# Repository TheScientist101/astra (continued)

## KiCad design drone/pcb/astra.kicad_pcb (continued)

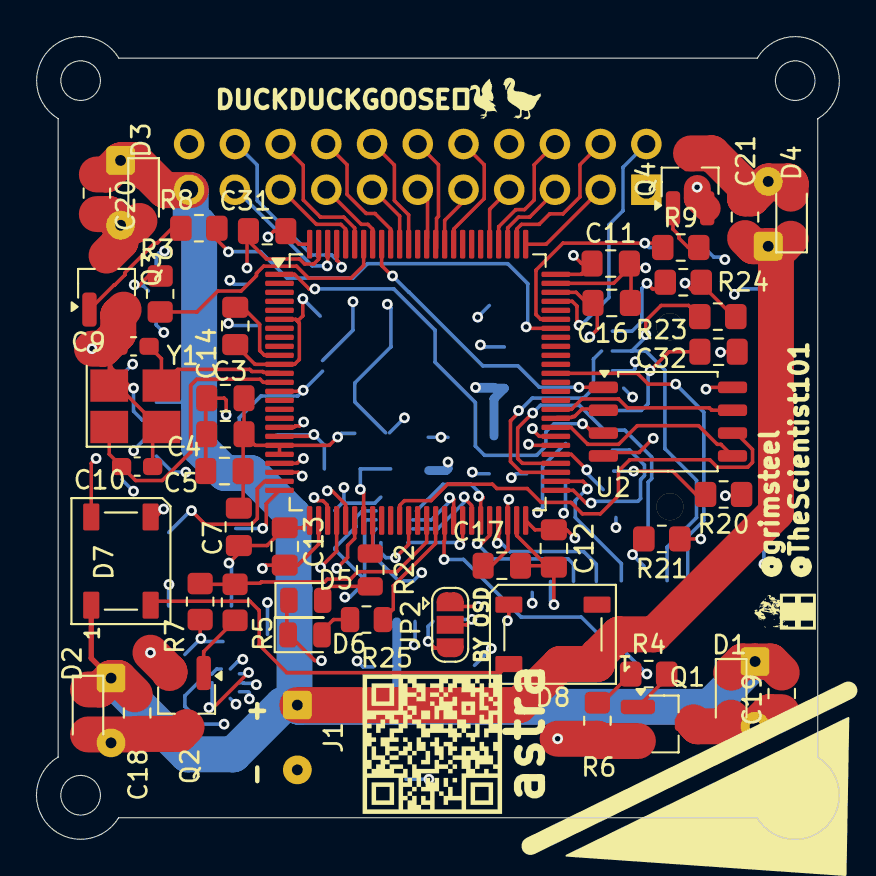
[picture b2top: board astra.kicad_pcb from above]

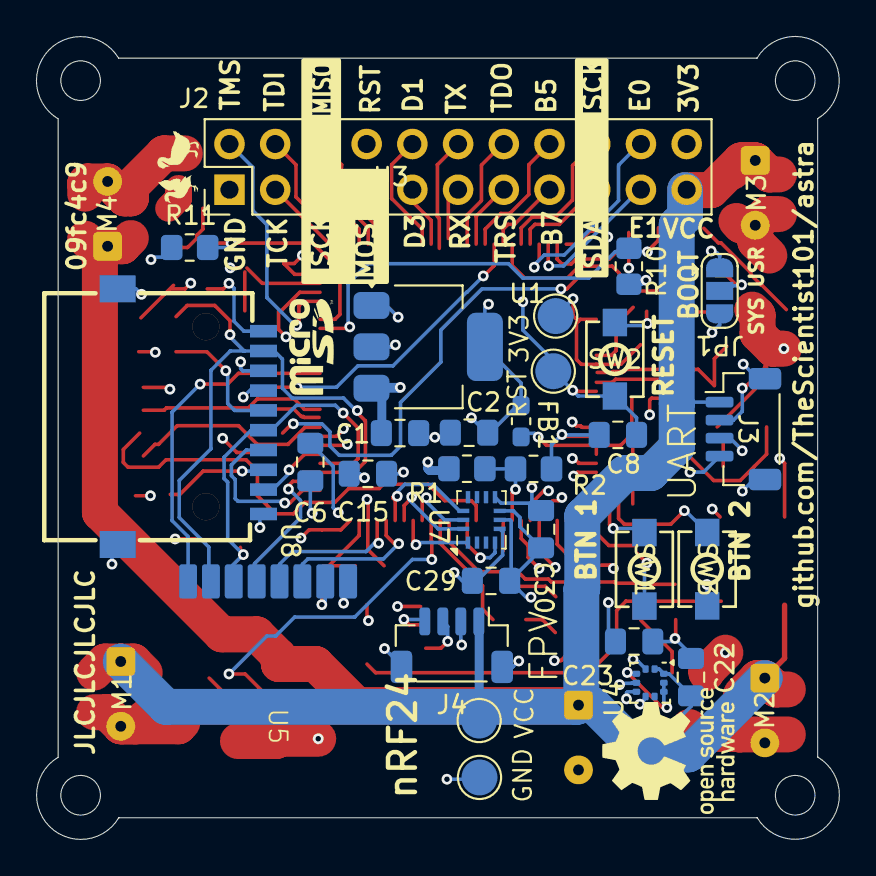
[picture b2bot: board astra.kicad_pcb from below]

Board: 4 copper layers, 44.6 x 44.6 mm, 83 parts (34 on the bottom side), 79 nets.

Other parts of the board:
QR*****: https://github.com/TheScientist101/astra; qrcode

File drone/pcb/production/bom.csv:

Designator,Footprint,Quantity,Value,LCSC Part #
"C1, C2",0805,2,10uF,
"C10, C9",0603,2,3.9pF,
"C11, C12, C13, C14, C18, C19, C20, C21, C22, C23, C29, C30, C31, C32, C4, C6, C7, C8",0805,18,100nF,
C15,0805,1,4.7uF,
"C16, C17",0805,2,0.2uF,
"C3, C5",0805,2,1uF,
"D1, D2, D3, D4",D_SOD-323_HandSoldering,4,1N4148,
"D5, D6",0805,2,LED,
"D7, D8",LED_WS2812B_PLCC4_5.0x5.0mm_P3.2mm,2,WS2812B,
FB1,0603,1,601T05,
J1,SolderWire-0.1sqmm_1x02_P3.6mm_D0.4mm_OD1mm,1,Conn_01x02_Pin,
J2,PinHeader_2x11_P2.54mm_Vertical,1,Conn_02x11_Odd_Even,
"J3, J4",JST_SH_BM04B-SRSS-TB_1x04-1MP_P1.00mm_Vertical,2,Conn_01x04_MountingPin,
"M1, M2, M3, M4",SolderWire-0.1sqmm_1x02_P3.6mm_D0.4mm_OD1mm,4,Motor_DC,
"Q1, Q2, Q3, Q4",SOT-23_Handsoldering,4,AO3400A,
"R1, R2",0805,2,100k,
"R10, R11, R20, R21, R23, R24, R3, R6, R7",0805,9,10k,
"R22, R25",0805,2,1k,
"R4, R5, R8, R9",0805,4,220,
"SW1, SW2, SW3",SW-SMD_L4.0-W2.9-LS5.0,3,SW_Push,
TP4,TestPoint_Pad_D2.0mm,1,TP_GND,
U1,SOT-223-3_TabPin2,1,TLV1117LV33DCYR,
U2,SOIC-8_5.3x5.3mm_P1.27mm,1,W25Q64JVSSIQ_C179171,
U3,LQFP-100_14x14mm_P0.5mm,1,STM32H750VBTx,
U4,ST_HLGA-10_2x2mm_P0.5mm_LayoutBorder3x2y,1,BMP388,
U5,nRF24L01_SMD_Breakout,1,NRF24L01_Breakout,
U7,Bosch_LGA-14_3x2.5mm_P0.5mm,1,BMI270,
U8,SIM-SMD_HYCW110-TF10-180B,1,HYCW110-TF10-180B,
Y1,Crystal_SMD_3225-4Pin_3.2x2.5mm_HandSoldering,1,25 MHz,

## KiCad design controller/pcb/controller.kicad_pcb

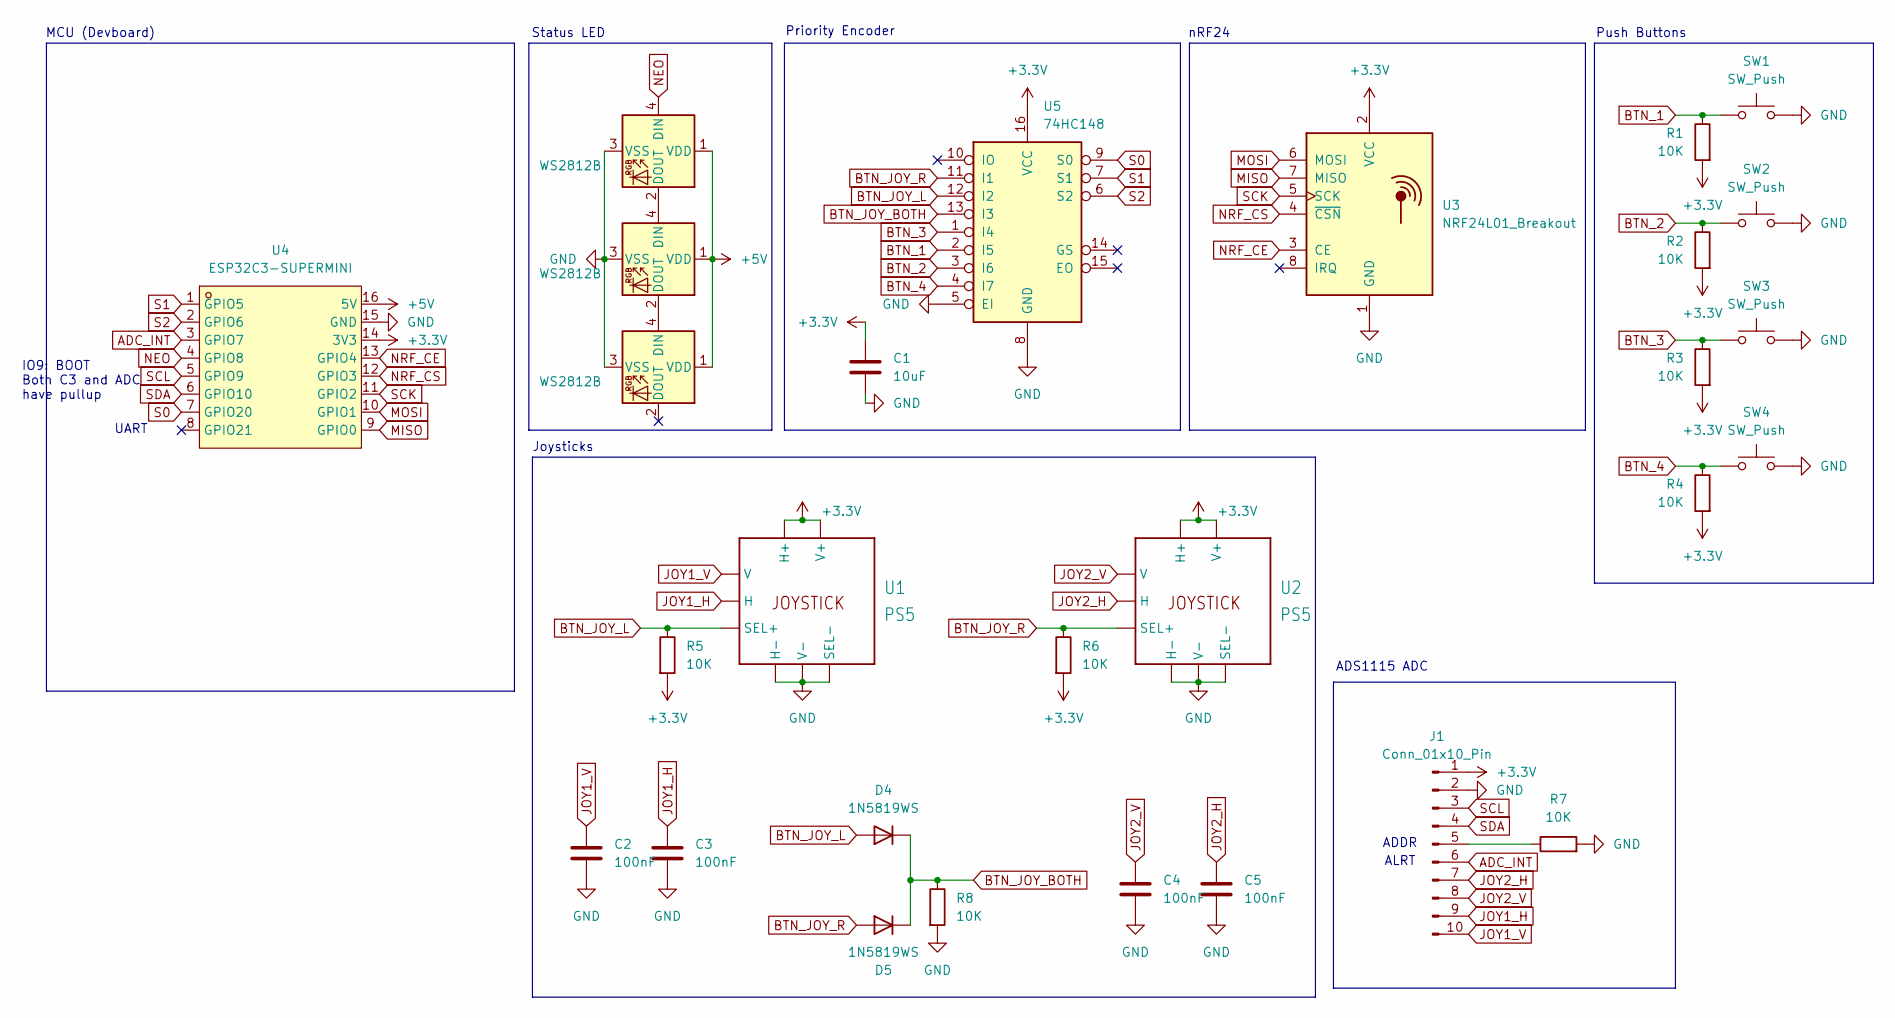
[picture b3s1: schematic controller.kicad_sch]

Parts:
C1: 10uF; C_0805_2012Metric
C2, C3, C4, C5: 100nF; C_0805_2012Metric
D1, D2, D3: WS2812B; LED_WS2812B_PLCC4_5.0x5.0mm_P3.2mm
D4, D5: 1N5819WS; D_DO-41_SOD81_P7.62mm_Horizontal
J1: Conn_01x10_Pin; PinHeader_1x10_P2.54mm_Vertical
R1, R2, R3, R4, R5, R6, R7, R8: 10K; R_0805_2012Metric
SW1, SW2, SW3, SW4: SW_Push; SW_PUSH-12mm
U1, U2: PS5; Joystick
U3: NRF24L01_Breakout; nRF24L01_SMD_Breakout
U4: ESP32C3-SUPERMINI; ESP32-C3-SuperMini; LCSC Part C9900147397
U5: 74HC148; SOP-16_3.9x9.9mm_P1.27mm

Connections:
+3.3V: C1.1, J1.1, R1.2, R2.2, R3.2, R4.2, R5.2, R6.2, U1.3 (H+), U1.3' (V+), U2.3 (H+), U2.3' (V+), U3.2 (VCC), U4.14 (3V3), U5.16 (VCC)
+5V: D1.1 (VDD), D2.1 (VDD), D3.1 (VDD), U4.16 (5V)
ADC_INT: J1.6, U4.3 (GPIO7)
BTN_1: R1.1, SW1.1, U5.2 (I5)
BTN_2: R2.1, SW2.1, U5.3 (I6)
BTN_3: R3.1, SW3.1, U5.1 (I4)
BTN_4: R4.1, SW4.1, U5.4 (I7)
BTN_JOY_BOTH: D4.1 (K), D5.1 (K), R8.1, U5.13 (I3)
BTN_JOY_L: D4.2 (A), R5.1, U1.a (SEL+), U5.12 (I2)
BTN_JOY_R: D5.2 (A), R6.1, U2.a (SEL+), U5.11 (I1)
GND: C1.2, C2.2, C3.2, C4.2, C5.2, D1.3 (VSS), D2.3 (VSS), D3.3 (VSS), J1.2, R7.2, R8.2, SW1.2, SW2.2, SW3.2, SW4.2, U1.1 (H-), U1.1' (V-), U1.c (SEL-), U2.1 (H-), U2.1' (V-), U2.c (SEL-), U3.1 (GND), U4.15 (GND), U5.5 (EI), U5.8 (GND)
JOY1_H: C3.1, J1.9, U1.2 (H)
JOY1_V: C2.1, J1.10, U1.2' (V)
JOY2_H: C5.1, J1.7, U2.2 (H)
JOY2_V: C4.1, J1.8, U2.2' (V)
MISO: U3.7 (MISO), U4.9 (GPIO0)
MOSI: U3.6 (MOSI), U4.10 (GPIO1)
NEO: D1.4 (DIN), U4.4 (GPIO8)
NRF_CE: U3.3 (CE), U4.13 (GPIO4)
NRF_CS: U3.4 (~CSN), U4.12 (GPIO3)
unnamed: D1.2 (DOUT), D2.4 (DIN)
unnamed: D2.2 (DOUT), D3.4 (DIN)
unnamed: J1.5, R7.1
S0: U4.7 (GPIO20), U5.9 (S0)
S1: U4.1 (GPIO5), U5.7 (S1)
S2: U4.2 (GPIO6), U5.6 (S2)
SCK: U3.5 (SCK), U4.11 (GPIO2)
SCL: J1.3, U4.5 (GPIO9)
SDA: J1.4, U4.6 (GPIO10)

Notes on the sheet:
Joysticks
Status LED
Push Buttons
UART
ALRT
nRF24
Priority Encoder
IO9: BOOT Both C3 and ADC have pullup
ADDR
MCU (Devboard)
ADS1115 ADC

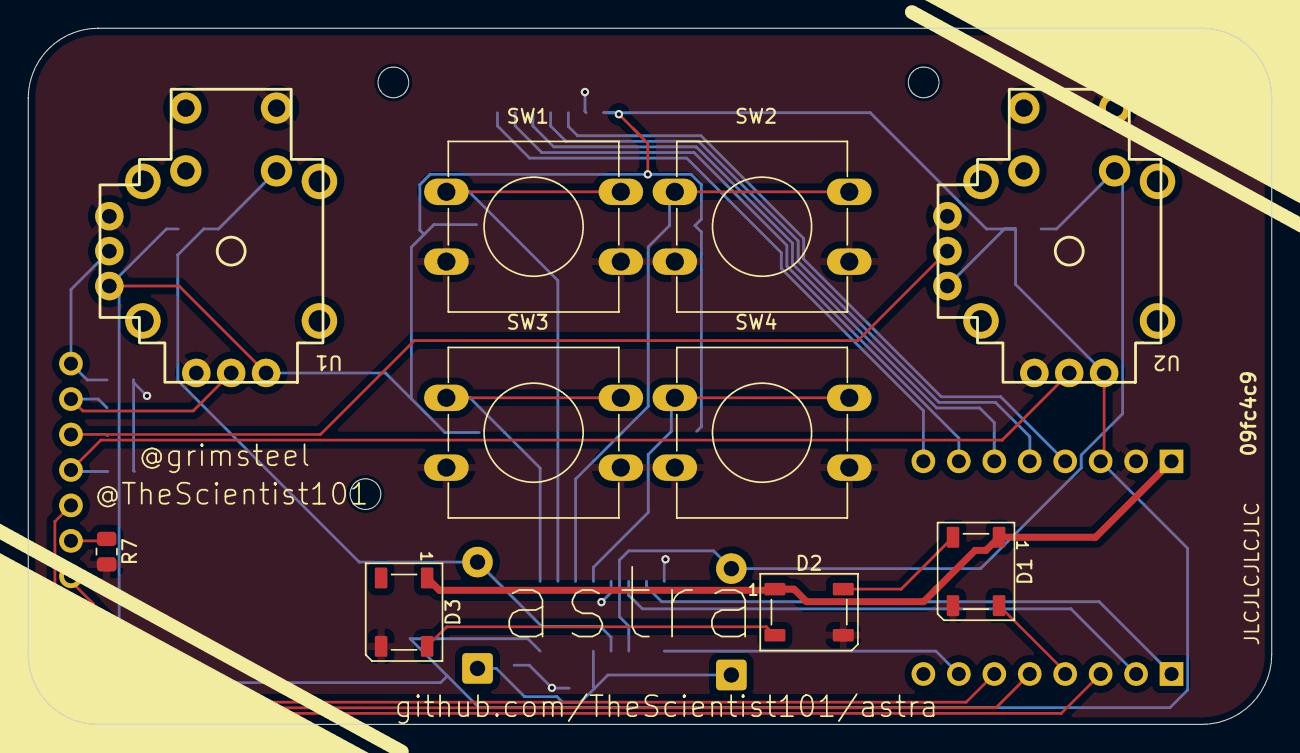
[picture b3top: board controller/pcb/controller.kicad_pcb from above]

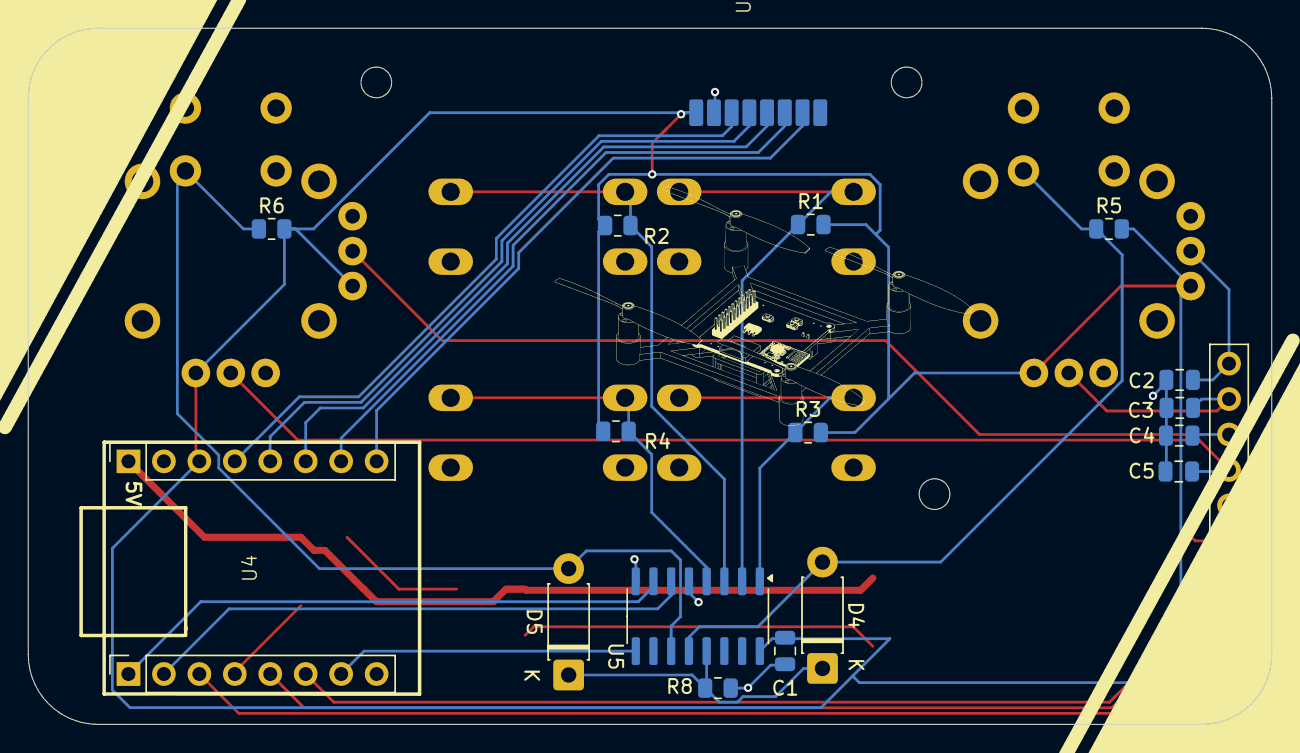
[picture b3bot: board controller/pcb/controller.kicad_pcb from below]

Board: 2 copper layers, 89.1 x 49.9 mm, 28 parts (18 on the bottom side), 29 nets.

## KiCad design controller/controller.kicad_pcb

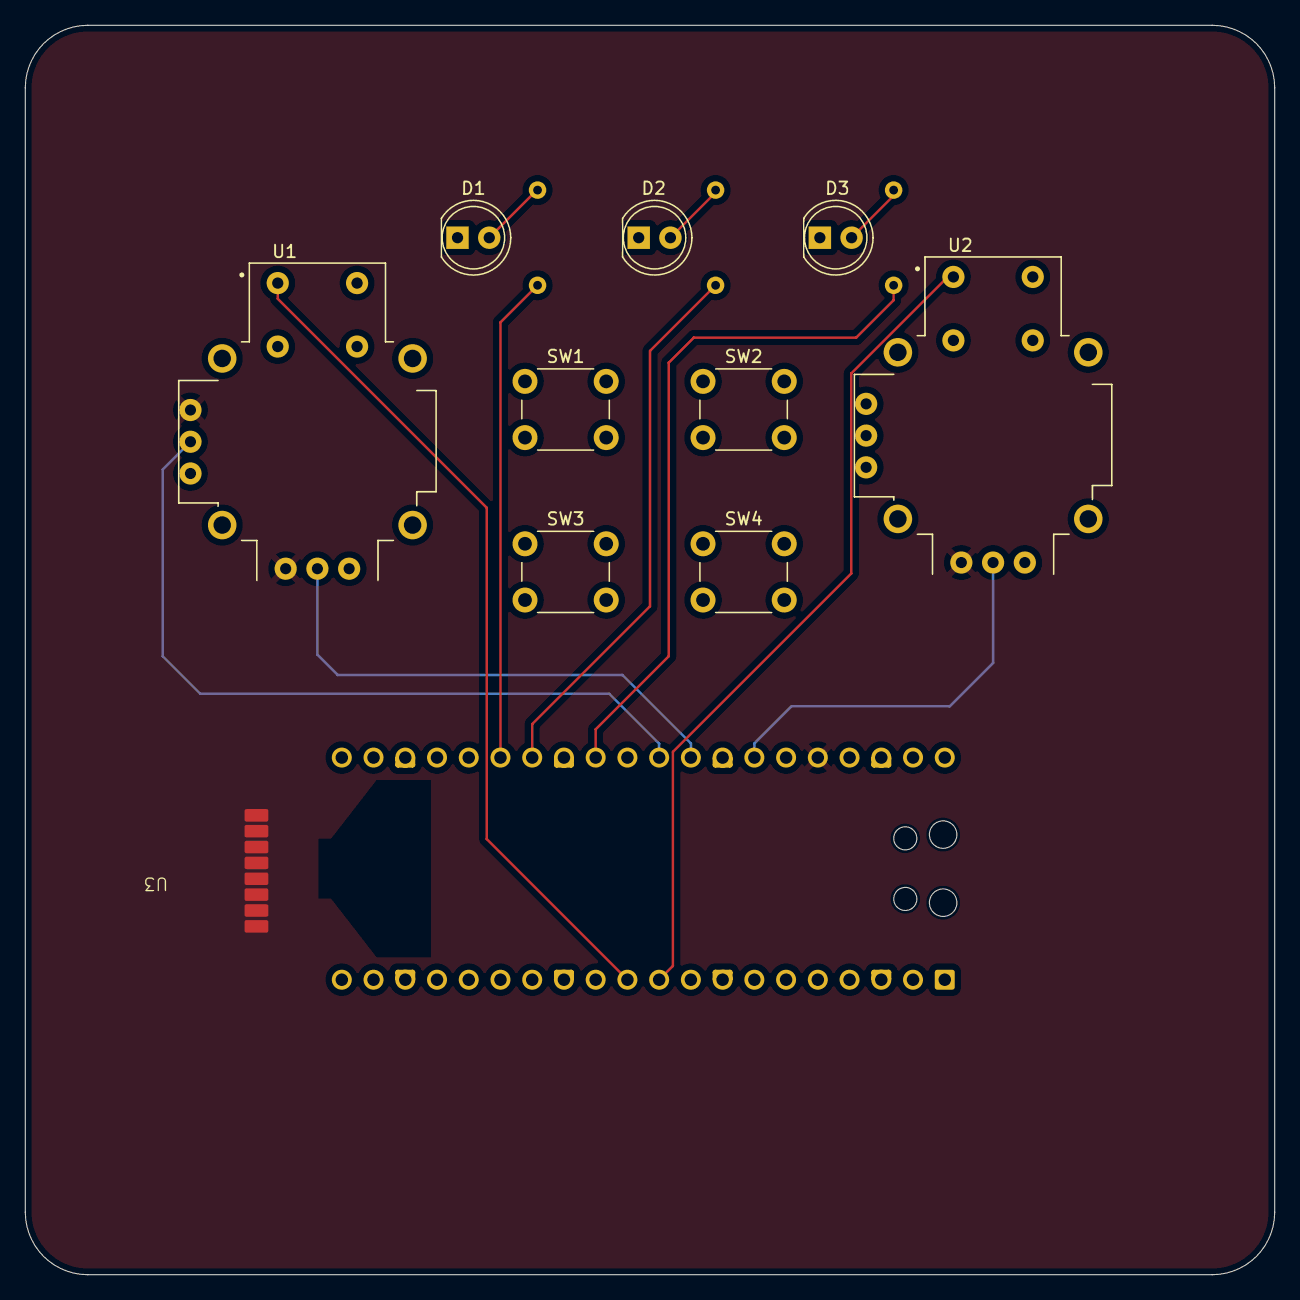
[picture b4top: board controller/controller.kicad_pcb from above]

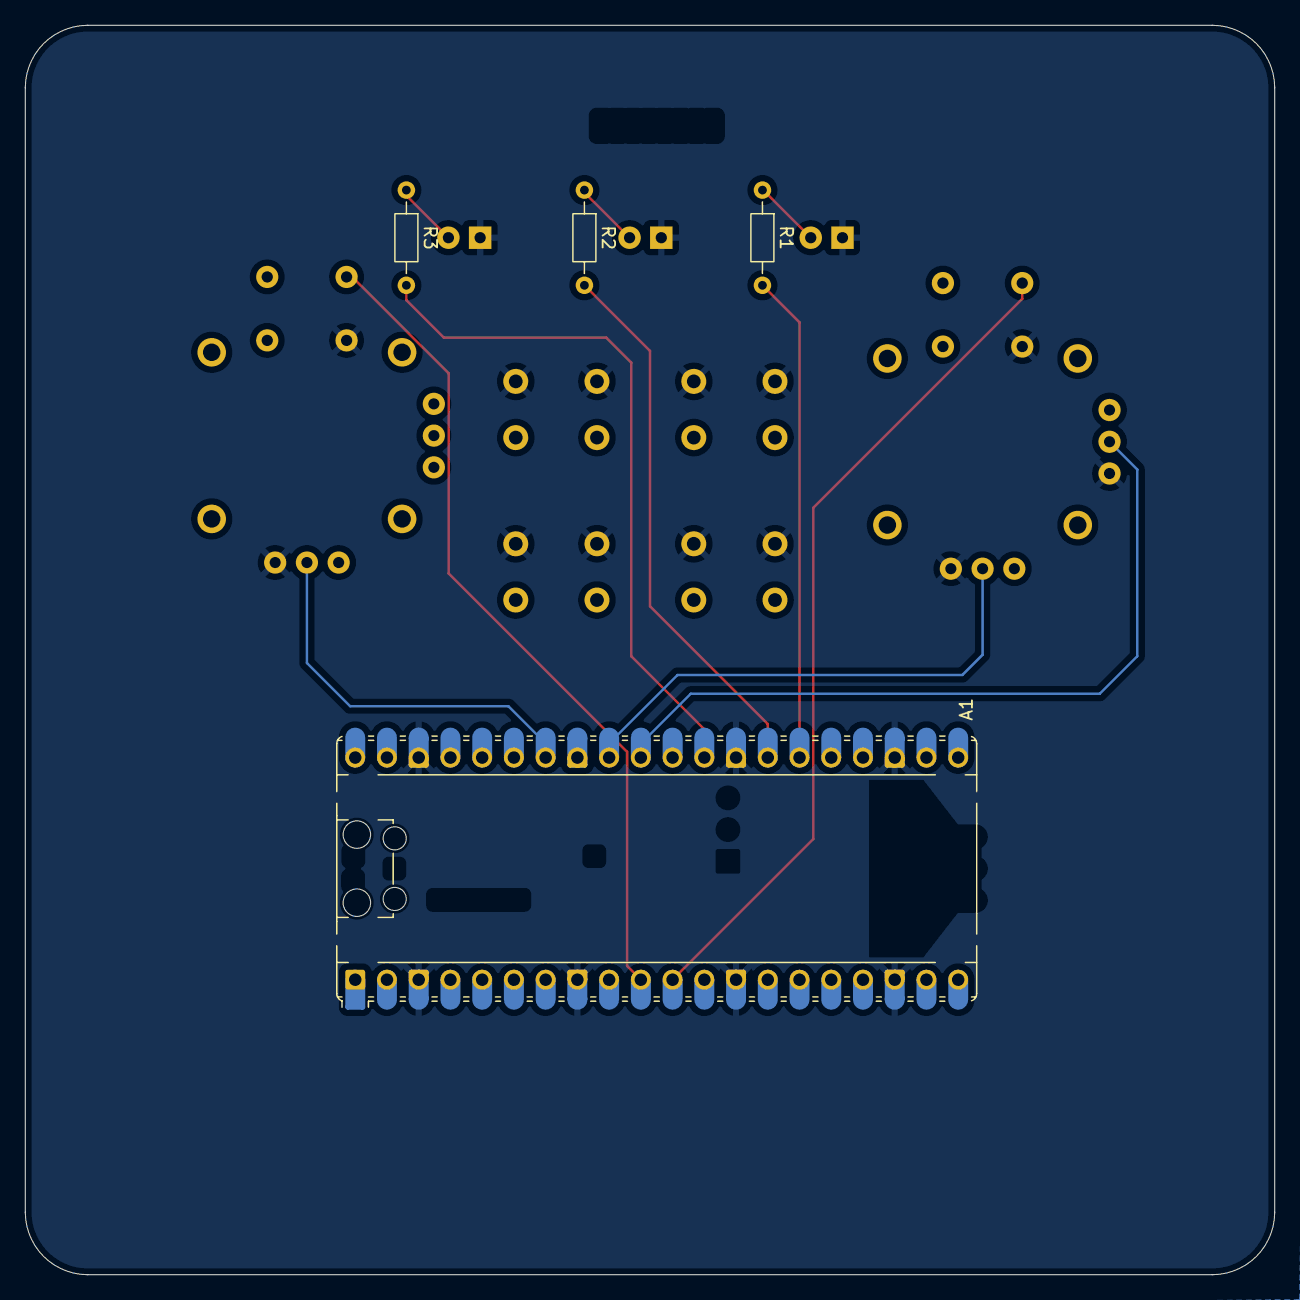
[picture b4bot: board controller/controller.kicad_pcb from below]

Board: 2 copper layers, 100.0 x 100.0 mm, 14 parts (4 on the bottom side), 22 nets.

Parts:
A1: RaspberryPi_Pico; RaspberryPi_Pico_Common_Unspecified
D1, D2, D3: LED; LED_D5.0mm
R1, R2, R3: 1k; R_Axial_DIN0204_L3.6mm_D1.6mm_P7.62mm_Horizontal
SW1, SW2, SW3, SW4: SW_Push; SW_PUSH_6mm
U1, U2: COM-09032; XDCR_COM-09032
U3: NRF24L01_Breakout; nRF24L01_SMD_Breakout

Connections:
+3.3V: A1.36 (3V3), U1.H1 (H+), U1.V1 (V+), U2.H1 (H+), U3.2 (VCC)
BTN1: A1.5 (GPIO3), SW1.2
BTN2: A1.6 (GPIO4), SW2.2
BTN3: A1.7 (GPIO5), SW3.2
BTN4: A1.9 (GPIO6), SW4.2
GND: A1.3 (GND), A1.8 (GND), A1.13 (GND), A1.18 (GND), A1.23 (GND), A1.28 (GND), A1.38 (GND), D1.1 (K), D2.1 (K), D3.1 (K), SW1.1, SW2.1, SW3.1, SW4.1, U1.B2A (SEL-), U1.H3 (H-), U1.V3 (V-), U2.B2A (SEL-), U2.H3 (H-), U3.1 (GND)
JOY1_BTN: A1.11 (GPIO8), U1.B1A (SEL+)
JOY1_H: A1.32 (GPIO27_ADC1), U1.H2 (H)
JOY1_V: A1.31 (GPIO26_ADC0), U1.V2 (V)
JOY2_BTN: A1.10 (GPIO7), U2.B1A (SEL+)
JOY2_H: A1.34 (GPIO28_ADC2), U2.H2 (H)
LED1: A1.26 (GPIO20), R1.2
LED2: A1.27 (GPIO21), R2.2
LED3: A1.29 (GPIO22), R3.2
MISO: A1.21 (GPIO16), U3.7 (MISO)
MOSI: A1.25 (GPIO19), U3.6 (MOSI)
NRF_CE: A1.17 (GPIO13), U3.3 (CE)
NRF_CS: A1.16 (GPIO12), U3.4 (~CSN)
unnamed: D1.2 (A), R1.1
unnamed: D2.2 (A), R2.1
unnamed: D3.2 (A), R3.1
SCK: A1.24 (GPIO18), U3.5 (SCK)

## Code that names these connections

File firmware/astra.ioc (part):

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Mcu.Name=STM32H750VBTx
Mcu.Package=LQFP100
Mcu.UserName=STM32H750VBTx
PA0.GPIOParameters=GPIO_Label
PA0.GPIO_Label=DDG_MAGIC_2
PA0.Signal=GPIO_Output
PA1.GPIOParameters=GPIO_Label
PA1.GPIO_Label=DDG_MAGIC_3
PA1.Signal=GPIO_Output
PA10.Signal=S_TIM1_CH3
PA11.Signal=S_TIM1_CH4
PA13\ (JTMS/SWDIO).Mode=JTAG_5_pins
PA13\ (JTMS/SWDIO).Signal=DEBUG_JTMS-SWDIO
PA14\ (JTCK/SWCLK).Mode=JTAG_5_pins
PA14\ (JTCK/SWCLK).Signal=DEBUG_JTCK-SWCLK
PA15\ (JTDI).Mode=JTAG_5_pins
PA15\ (JTDI).Signal=DEBUG_JTDI
PA2.GPIOParameters=GPIO_Label
PA2.GPIO_Label=DDG_MAGIC_4
PA2.Signal=GPIO_Output
PA3.GPIOParameters=GPIO_Label
PA3.GPIO_Label=DDG_MAGIC_5
PA3.Signal=GPIO_Output
PA4.Mode=Slave_10_bits_External_Synchro
PA4.Signal=DCMI_HSYNC
PA6.Mode=Slave_10_bits_External_Synchro
PA6.Signal=DCMI_PIXCLK
PA7.GPIOParameters=GPIO_Label
PA7.GPIO_Label=STATUS_LED
PA7.Signal=GPIO_Output
PA9.Mode=Slave_10_bits_External_Synchro
PA9.Signal=DCMI_D0
PB10.Mode=I2C
PB10.Signal=I2C2_SCL
PB11.Mode=I2C
PB11.Signal=I2C2_SDA
PB12.GPIOParameters=GPIO_Label
PB12.GPIO_Label=SD_CS
PB12.Mode=NSS_Signal_Hard_Output
PB12.Signal=SPI2_NSS
PB13.Mode=Full_Duplex_Master
PB13.Signal=SPI2_SCK
PB14.Mode=Full_Duplex_Master
PB14.Signal=SPI2_MISO
PB15.Mode=Full_Duplex_Master
PB15.Signal=SPI2_MOSI
PB2.Mode=Single Bank 1
PB2.Signal=QUADSPI_CLK
PB3\ (JTDO/TRACESWO).Mode=JTAG_5_pins
PB3\ (JTDO/TRACESWO).Signal=DEBUG_JTDO-SWO
PB4\ (NJTRST).Mode=JTAG_5_pins
PB4\ (NJTRST).Signal=DEBUG_JTRST
PB6.Mode=Single Bank 1
PB6.Signal=QUADSPI_BK1_NCS
PB7.Mode=Slave_10_bits_External_Synchro
PB7.Signal=DCMI_VSYNC
PB8.Mode=I2C
PB8.Signal=I2C1_SCL
PB9.Mode=I2C
PB9.Signal=I2C1_SDA
PC10.Mode=Slave_10_bits_External_Synchro
PC10.Signal=DCMI_D8
PC11.Mode=Slave_10_bits_External_Synchro
PC11.Signal=DCMI_D4
PC12.Mode=Slave_10_bits_External_Synchro
PC12.Signal=DCMI_D9
PC3_C.GPIOParameters=GPIO_Label
PC3_C.GPIO_Label=DDG_MAGIC_1
PC3_C.Signal=GPIO_Output
PC4.GPIOParameters=GPIO_Label
PC4.GPIO_Label=BAT_MEASURE
PC4.Signal=ADCx_INP4
PC7.Mode=Slave_10_bits_External_Synchro
PC7.Signal=DCMI_D1
PD11.Mode=Single Bank 1
PD11.Signal=QUADSPI_BK1_IO0
PD12.Mode=Single Bank 1
PD12.Signal=QUADSPI_BK1_IO1
PD13.Mode=Single Bank 1
PD13.Signal=QUADSPI_BK1_IO3
PD3.Mode=Slave_10_bits_External_Synchro
PD3.Signal=DCMI_D5
PD6.GPIOParameters=GPIO_Label
PD6.GPIO_Label=DCMI_PWDN
PD6.Signal=GPIO_Output
PD7.GPIOParameters=GPIO_Label
PD7.GPIO_Label=DCMI_RST
PD7.Signal=GPIO_Output
PE0.Mode=Slave_10_bits_External_Synchro
PE0.Signal=DCMI_D2
PE1.Mode=Slave_10_bits_External_Synchro
PE1.Signal=DCMI_D3
PE11.Signal=S_TIM1_CH2
PE12.GPIOParameters=GPIO_Label
PE12.GPIO_Label=NRF_CS
PE12.Signal=GPIO_Output
PE13.GPIOParameters=GPIO_Label
PE13.GPIO_Label=NRF_CE
PE13.Signal=GPIO_Output
PE2.Mode=Single Bank 1
PE2.Signal=QUADSPI_BK1_IO2
PE5.Mode=Slave_10_bits_External_Synchro
PE5.Signal=DCMI_D6
PE6.Mode=Slave_10_bits_External_Synchro
PE6.Signal=DCMI_D7
PE9.Signal=S_TIM1_CH1
PH0-OSC_IN\ (PH0).Mode=HSE-External-Oscillator
PH0-OSC_IN\ (PH0).Signal=RCC_OSC_IN
PH1-OSC_OUT\ (PH1).Mode=HSE-External-Oscillator
PH1-OSC_OUT\ (PH1).Signal=RCC_OSC_OUT
RCC.HSE_VALUE=25000000
RCC.SYSCLKFreq_VALUE=240000000
RCC.SYSCLKSource=RCC_SYSCLKSOURCE_PLLCLK
board=custom

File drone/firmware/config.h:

/*
 * This file is part of Betaflight.
 *
 * Betaflight is free software. You can redistribute this software
 * and/or modify this software under the terms of the GNU General
 * Public License as published by the Free Software Foundation,
 * either version 3 of the License, or (at your option) any later
 * version.
 *
 * Betaflight is distributed in the hope that it will be useful,
 * but WITHOUT ANY WARRANTY; without even the implied warranty of
 * MERCHANTABILITY or FITNESS FOR A PARTICULAR PURPOSE.
 *
 * See the GNU General Public License for more details.
 *
 * You should have received a copy of the GNU General Public
 * License along with this software.
 *
 * If not, see <http://www.gnu.org/licenses/>.
 */

#pragma once

#define FC_TARGET_MCU     STM32H750

#define BOARD_NAME        ASTRA
#define MANUFACTURER_ID   DUCK

#define TARGET_BOARD_IDENTIFIER "ASTR"
#define USBD_PRODUCT_STRING "Astra"

#define FC_VMA_ADDRESS    0x97CE0000

#define EEPROM_SIZE 8192

#define USE_SPRACING_PERSISTENT_RTC_WORKAROUND

#define USE_USB_ID

// ======== PERIPHERAL CONFIGURATION =======

#define USE_QUADSPI
#define USE_QUADSPI_DEVICE_1
#define QUADSPI1_SCK_PIN PB2
#define QUADSPI1_BK1_IO0_PIN PD11
#define QUADSPI1_BK1_IO1_PIN PD12
#define QUADSPI1_BK1_IO2_PIN PE2
#define QUADSPI1_BK1_IO3_PIN PD13
#define QUADSPI1_BK1_CS_PIN  PB6
#define QUADSPI1_BK2_IO0_PIN NONE
#define QUADSPI1_BK2_IO1_PIN NONE
#define QUADSPI1_BK2_IO2_PIN NONE
#define QUADSPI1_BK2_IO3_PIN NONE
#define QUADSPI1_BK2_CS_PIN  NONE
#define QUADSPI1_MODE QUADSPI_MODE_BK1_ONLY
#define QUADSPI1_CS_FLAGS (QUADSPI_BK1_CS_HARDWARE | QUADSPI_BK2_CS_NONE | QUADSPI_CS_MODE_LINKED)

// Barometer
#define USE_SPI_DEVICE_1
#define SPI1_SCK_PIN            PA5
#define SPI1_SDI_PIN            PA6
#define SPI1_SDO_PIN            PA7
#define SPI1_NSS_PIN            PA4

// NRF, SD card
#define USE_SPI_DEVICE_2
#define SPI2_SCK_PIN            PB13
#define SPI2_SDI_PIN            PB14
#define SPI2_SDO_PIN            PB15

// DDG
#define USE_SPI_DEVICE_3
#define SPI3_SCK_PIN            PC10
#define SPI3_SDI_PIN            PC11
#define SPI3_SDO_PIN            PC12

// gyro
#define USE_SPI_DEVICE_4
#define SPI4_SCK_PIN            PE12
#define SPI4_SDI_PIN            PE13
#define SPI4_SDO_PIN            PE14

// DDG
#define USE_I2C_DEVICE_1
#define I2C1_SCL_PIN PB8
#define I2C1_SDA_PIN PB9
//  #define I2C_DEVICE I2CDEV_1

// DDG
#define UART2_TX_PIN         PD5
#define UART2_RX_PIN         PD6
#define SERIALRX_UART SERIAL_PORT_USART2

// Standalone JST
#define UART4_TX_PIN         PA0
#define UART4_RX_PIN         PA1

// ======== DEVICE CONFIGURATION ========

// Quad SPI Flash (64 MB)
#define FLASH_QUADSPI_INSTANCE  QUADSPI
#define USE_FLASH
#define USE_FLASH_QUADSPI
#define USE_FLASH_M25P16
#define FLASH_CS_PIN            PB6
#define CONFIG_IN_EXTERNAL_FLASH
#define USE_FIRMWARE_PARTITION

// ADC -  Battery Voltage Measurement
#define USE_ADC
#define ADC_INSTANCE                    ADC1
#define DEFAULT_CURRENT_METER_SOURCE    CURRENT_METER_ADC
//#define DEFAULT_VOLTAGE_METER_SOURCE    VOLTAGE_METER_ADC
//#define DEFAULT_CURRENT_METER_SCALE     100
#define DEFAULT_VOLTAGE_METER_SCALE     110
#define ADC_VBAT_PIN                    PC4
//#define ADC_RSSI_PIN         PC4
//#define ADC_CURR_PIN         PC0
//#define ADC_EXTERNAL1_PIN    PC5
//#define DEFAULT_FEATURES FEATURE_RSSI_ADC

// MicroSD Card - SPI2
#define USE_SDCARD
#define USE_SDCARD_SPI
#define SDCARD_SPI_CS_PIN    PB12
#define SDCARD_DETECT_PIN    PD8
#define SDCARD_DETECT_INVERTED
#define DEFAULT_BLACKBOX_DEVICE BLACKBOX_DEVICE_SDCARD
#define SDCARD_SPI_INSTANCE  SPI2

// Barometer - SPI1
#define USE_BARO
#define USE_BARO_BMP388
#define BARO_SPI_INSTANCE    SPI1
#define BARO_CS_PIN          PA4

// WS2812B
#define USE_LED_STRIP
#define LED_STRIP_PIN        PC3

// Motors - PWM TIM1
#define MOTOR1_PIN           PE9
#define MOTOR2_PIN           PE11
#define MOTOR3_PIN           PA10
#define MOTOR4_PIN           PA11

// RX - NRF24
#define USE_RX
#define USE_RX_NRF24
#define USE_RX_SPI
// protocol - can be customized
#define USE_RX_SYMA
#define RX_CE_PIN           PB10
#define RX_SPI_CS_PIN       PB11
#define RX_SPI_EXTI_PIN     PC7
#define RX_SPI_INSTANCE     SPI2
#define RX_NSS_PIN          RX_SPI_CS_PIN

// BMI270 - SPI4
#define USE_GYRO
#define USE_ACC
#define USE_ACCGYRO_BMI270
#define GYRO_1_EXTI_PIN      PE14
#define GYRO_1_SPI_INSTANCE  SPI4
#define GYRO_1_ALIGN         CW0_DEG_FLIP
#define GYRO_1_CS_PIN        PE7

// Status LEDs
#define LED0_PIN             PC5
#define LED1_PIN             PE10

// Custom Buttons
#define USE_BUTTONS
#define BUTTON_A_PIN            PA3
#define BUTTON_A_PIN_INVERTED
#define BUTTON_B_PIN            PA2
#define BUTTON_B_PIN_INVERTED

// ========= DMA CONFIGURATION =========

// TODO: figure out these once we get the board
#define ADC1_DMA_OPT            8
#define TIMUP1_DMA_OPT          0
#define TIMUP2_DMA_OPT          0
#define TIMUP3_DMA_OPT          0
#define TIMUP4_DMA_OPT          0
#define TIMUP5_DMA_OPT          0
#define TIMUP8_DMA_OPT          2

#define TIMER_PIN_MAPPING \
    TIMER_PIN_MAP(0, PA8, 1, 10) \
    TIMER_PIN_MAP(1, PB11, 1, 11) \
    TIMER_PIN_MAP(2, PB15, 2, -1) \
    TIMER_PIN_MAP(3, PE5, 1, 0) \
    TIMER_PIN_MAP(4, PE6, 1, -1) \
    TIMER_PIN_MAP(5, PA0, 2, 0) \
    TIMER_PIN_MAP(6, PA1, 2, 1) \
    TIMER_PIN_MAP(7, PA2, 2, 2) \
    TIMER_PIN_MAP(8, PA3, 2, 3) \
    TIMER_PIN_MAP(9, PB6, 2, 4) \
    TIMER_PIN_MAP(10, PB7, 2, 5) \
    TIMER_PIN_MAP(11, PC6, 2, 6) \
    TIMER_PIN_MAP(12, PC7, 2, 7) \
    TIMER_PIN_MAP(13, PD14, 1, 12) \
    TIMER_PIN_MAP(14, PD15, 1, -1) \
    TIMER_PIN_MAP(15, PA6, 1, 0) \
    TIMER_PIN_MAP(16, PA7, 2, 0) \
    TIMER_PIN_MAP(17, PB0, 2, 0) \
    TIMER_PIN_MAP(18, PB1, 2, 0)

#define TIMUP1_DMA_OPT 0
#define TIMUP2_DMA_OPT 0
#define TIMUP3_DMA_OPT 0
#define TIMUP4_DMA_OPT 0
#define TIMUP5_DMA_OPT 0
#define TIMUP8_DMA_OPT 2

// FPV stuff

//#define USE_MAX7456
//#define CAMERA_CONTROL_PIN   PE5
//#define MAX7456_SPI_CS_PIN   PE11
//#define MAX7456_SPI_INSTANCE SPI4

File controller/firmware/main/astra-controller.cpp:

#include <esp_timer.h>
#include <freertos/FreeRTOS.h>
#include <freertos/timers.h>
#include <driver/gpio.h>
#include <esp_log.h>
#include "led_strip.h"
#include "led_strip_types.h"
#include "i2cdev.h"
#include "v202_protocol.hpp"
#include "nrf24.hpp"
#include "joystick.hpp"

#define NEOPIXEL_GPIO GPIO_NUM_8
#define NUM_NEOPIXEL 3

// this is a UART pin - might need to be disabled
#define BUTTON_ENCODER_0 GPIO_NUM_20
#define BUTTON_ENCODER_1 GPIO_NUM_5
#define BUTTON_ENCODER_2 GPIO_NUM_6

#define ADC_SDA GPIO_NUM_10
#define ADC_SCL GPIO_NUM_9
#define ADC_INT GPIO_NUM_7

typedef enum {
  BTN_NONE = 0,
  BTN_JOY_R = 1,
  BTN_JOY_L = 2,
  BTN_JOY_BOTH = 3,
  BTN_3 = 4,
  BTN_1 = 5,
  BTN_2 = 6,
  BTN_4 = 7
} button_state_t;

// this essentially stores the currently pressed button number (1-7)
static button_state_t button_state = BTN_NONE;

/// Higher-level handler for buttons presses
static void button_press_handler(button_state_t button_pressed) {
  // TODO: unimplemented
  // note - this is called from an interrupt - use queues if delays or other long operations are needed
}

/// Button priority encoder interrupt handler
static void IRAM_ATTR button_isr_handler(void* arg) {
  gpio_num_t gpio_num = (gpio_num_t) (uint32_t) arg;
  // active-low, so invert
  int new_pin_state = !gpio_get_level(gpio_num);
  uint8_t new_button_state = button_state;

  // convert gpio number to bit index
  uint8_t bit;
  switch (gpio_num) {
    case BUTTON_ENCODER_0:
      bit = 0; break;
    case BUTTON_ENCODER_1:
      bit = 1; break;
    case BUTTON_ENCODER_2:
      bit = 2; break;
    default: return;
  }

  // clear
  new_button_state &= ~(1 << bit);
  // set
  new_button_state |= (new_pin_state << bit);

  if (new_button_state != button_state) {
    button_press_handler(button_state = (button_state_t) new_button_state);
  }
}

led_strip_handle_t init_neopixel() {
  // configure neopixel
  led_strip_config_t neopixel_config = {
    .strip_gpio_num = NEOPIXEL_GPIO,
    .max_leds = NUM_NEOPIXEL,
    .led_model = LED_MODEL_WS2812,
    .color_component_format = LED_STRIP_COLOR_COMPONENT_FMT_GRB,
    .flags = {
      .invert_out = false
    }
  };
  led_strip_rmt_config_t neopixel_rmt_config = {
    .clk_src = RMT_CLK_SRC_DEFAULT,
    .resolution_hz = 10 * 1000 * 1000, // 10 MHz
    .mem_block_symbols = 64,
    .flags = {
      .with_dma = false, // not available on C3
    }
  };
  led_strip_handle_t neopixel_handle = nullptr;
  ESP_ERROR_CHECK(led_strip_new_rmt_device(&neopixel_config, &neopixel_rmt_config, &neopixel_handle));
  // turn all off
  led_strip_clear(neopixel_handle);
  return neopixel_handle;
}

void init_buttons() {
  // configure button GPIOs
  gpio_config_t io_conf = {
    // rising or falling
    .pin_bit_mask = (1ULL << BUTTON_ENCODER_0) | (1ULL << BUTTON_ENCODER_1) | (1ULL << BUTTON_ENCODER_2),
    .mode = GPIO_MODE_INPUT,
    .pull_up_en = GPIO_PULLUP_ENABLE,
    .pull_down_en = GPIO_PULLDOWN_DISABLE,
    .intr_type = GPIO_INTR_ANYEDGE,
  };
  gpio_config(&io_conf);

  // register interrupt handlers
  gpio_isr_handler_add(BUTTON_ENCODER_0, button_isr_handler, (void*) BUTTON_ENCODER_0);
  gpio_isr_handler_add(BUTTON_ENCODER_1, button_isr_handler, (void*) BUTTON_ENCODER_1);
  gpio_isr_handler_add(BUTTON_ENCODER_2, button_isr_handler, (void*) BUTTON_ENCODER_2);
}

uint8_t map_v202_rotation(uint8_t joystick_value) {
  int8_t signed_value = (int8_t) (joystick_value - 128);

  // [-128, 0] gets mapped to [0, 128] (left)
  if (signed_value <= 0) return (uint8_t) (-signed_value);
  // (0, 127] gets mapped to (128, 255] (right)
  else return (uint8_t) (signed_value) + 0x80;
}

extern "C" void app_main(void)
{
  // setup per-pin interrupts
  ESP_ERROR_CHECK(gpio_install_isr_service(0));

  TaskHandle_t main_task = xTaskGetCurrentTaskHandle();

  led_strip_handle_t neopixel = init_neopixel();
  // LED 0 <- Red
  ESP_ERROR_CHECK(led_strip_set_pixel(neopixel, 0, 15, 0, 0));
  ESP_ERROR_CHECK(led_strip_set_pixel(neopixel, 1, 0, 16, 0));
  ESP_ERROR_CHECK(led_strip_set_pixel(neopixel, 2, 0, 0, 15));
  led_strip_refresh(neopixel);

  init_buttons();

  // configure TX
  V202 v202;
  // pins configured in defconfig
  NRF24 nrf24;
  v202.init(&nrf24, TX, TAER);
  uint8_t id[] = {0,0,0};
  v202.setTXId(id);
  
  ESP_ERROR_CHECK(i2cdev_init());

  // initialize joystick ADC
  Joystick joystick(ADC_SDA, ADC_SCL, ADC_INT);

  // start joystick main loop
  joystick.start(main_task);

  // wait for initialization
  ulTaskNotifyTakeIndexed(JOYSTICK_TASK_NOTIFY_INDEX, pdTRUE, portMAX_DELAY);

  // main loop
  while (true) {
    // transmitter mode 2
    uint8_t throttle = joystick.joy1_v;
    uint8_t yaw = map_v202_rotation(joystick.joy1_h);
    uint8_t pitch = map_v202_rotation(joystick.joy2_v);
    uint8_t roll = map_v202_rotation(joystick.joy2_h);

    ESP_LOGI("HI", "%d %d %d %d %d", throttle, yaw, pitch, roll, button_state);

    // TODO: do something here
    uint8_t flags = 0;
    v202.command(throttle, yaw, pitch, roll, flags);

    ESP_LOGI("HI", "send");

    vTaskDelay(1000 / portTICK_PERIOD_MS);
  }
}

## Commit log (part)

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2025-05-24 [journal] add entry for 5/23
2025-06-04 [bom] add initial BOM
2025-06-05 [bom] update some components
2025-06-05 [bom] component research
2025-06-05 [journal] add entry for 6/4
2025-06-11 [bom] final draft of components
2025-06-11 [journal] add entry for 6/10
2025-06-11 add kicad project
2025-06-11 add subsheets
2025-06-11 [pcb] Started STM32 schematic
2025-06-11 [journal] add 6/10 schematic entry
2025-06-11 [pcb] More STM32 power
2025-06-11 [journal] add entry for 6/11
2025-06-11 [pcb] initial motor controller
2025-06-13 [pcb] start transceiver implementation
2025-06-13 [journal] added journal entry for 6/12
2025-06-13 [pcb] motor controllers, label/group cleanup
2025-06-13 [journal] add remaining day 3 screenshots
2025-06-13 [journal] update totals
2025-06-13 [pcb] improve MCU analog power, battery voltage measurement, JTAG header
2025-06-14 [firmware] add initial cube mx project
2025-06-14 [firmware] more cube updates
2025-06-14 [pcb] gpio selection, camera, crystal
    - Each motors is connected to a channel of TIM1
    - The battery voltage divider is connected to ADC1
    - The NRF24 is connected to SPI2
    - Added OV5640 camera (FPC connector) + LDOs
2025-06-15 [pcb] add imu
2025-06-15 [journal] add entry for 6/14
2025-06-15 [firmware] clock updates for i2c
2025-06-16 [bom] pcb components and [pcb] assign footprints
2025-06-19 [pcb] initial layout and power routing
2025-06-20 [pcb] and [bom] add micro secure digital card interface socket connector
2025-06-20 [pcb] more routing
2025-06-20 [journal] add routing screenshot
2025-06-20 [journal] add entry for 6/20
2025-06-22 [pcb] 4 layer routing
2025-06-30 [pcb] continue routing - motors, camera, battery
2025-06-30 [journal] add entry for 6/30
2025-07-01 [pcb] invented the cutting edge, extremely innovative monke and ddg connectors
2025-07-01 [pcb] changed switches to optimize pcb layout
2025-07-02 [pcb] finish routing
2025-07-03 [pcb] add some 3d mooodels
2025-07-03 [journal] add entry for 07/03
2025-07-05 [pcb] controller schematic, intial layout
2025-07-06 [pcb] controller layout
2025-07-06 [bom] add dpdt switch and 24 MHz crystal, [firmware] update ioc pin assignments
2025-07-06 [pcb] silkscreen labels and logos
2025-07-07 [pcb] add status led
2025-07-07 [firmware] generate initial structure with STM32CubeMX
2025-07-07 [pcb] small fixes and improvements
    - add two status LEDs
    - move silkscreen labels for better visibility
    - add more silkcreen logos/credits
    - fix nrf footprint, add rf keepout zone
    - add mounting holes
2025-07-09 [pcb] remove on-board camera
    - remove camera and all supporting components (we'll be using an external dedicated board)
    - extend DDG header
    - make PCB smaller
    - add more silkscreen labels
2025-07-09 [pcb] utilize unused gpios, silkscreen improvements and [journal] add entry for 7/9
2025-07-09 [docs] add license
2025-07-10 [pcb] some more silkscreen improvements
2025-07-10 [firmware] remove old STM32 project, finish betaflight config, add build instructions
2025-07-10 [pcb] switch bmi270 to SPI, wire interrupt pins and SD chip detect
2025-07-12 [firmware] add nRF24 RX config
2025-07-13 [pcb] change pico for c3 supermini and use priority encoder for more inputs
2025-07-13 [pcb] dogbone board edge for mounting holes
2025-07-13 [pcb] finish controller schematic, route controller pcb
2025-07-15 [pcb] various routing improvements
2025-07-15 [pcb] reroute front traces under stm32
2025-07-15 [journal] add journal entry for 7/10 to 7/14
2025-07-16 [journal] add entry for 07/16
2025-07-18 reorganize project directories
2025-07-19 [firmware] add v202 protocl and nrf24 driver code
2025-07-19 [controller] add smoothing caps to ADC lines
2025-07-19 [controller] use higher quality external ADC
2025-07-19 [controller] firmware: buttons, ws2812b, old joystick ADC
2025-07-20 [controller] finish firmware, implement better ADC sampling w/ interrupt
2025-07-20 [journal] add entry for 7/19
2025-07-20 [controller] fix firmware linking issues
2025-07-21 [pcb] add JST FPV connector
2025-07-21 [docs] improve readme
2025-07-21 [docs] fix some numbers and styling in readme
2025-07-21 [bom] change battery and [controller] add button 3d files
2025-07-21 [cad] add drone cad files
2025-07-21 [pcb] add production files
2025-07-21 [journal] add entry for siddhant 7/20
2025-07-21 [pcb] change footprint for joystick on controller
2025-07-21 [cad] design controller case
2025-07-21 [journal] add second entry for 07/20
2025-07-21 [pcb] update battery connector footprint
2025-07-21 [cad] add additional mounting hole for controller
2025-07-21 [pcb] add additional mounting hole for controller
2025-07-21 [journal] update journal entry for 07/20
2025-07-21 [bom] add bom CSV, fix quantities
2025-07-21 [docs] add controller photos and "why" to readme
2025-07-21 [journal] add initial entry for 07/21
2025-07-21 [docs] Fix typo in license
2025-07-21 [bom] tax + shipping and [controller] add silkscreen
2025-07-21 [journal] rename project name to be lowercase
2025-07-25 Replace usernames with names in journal
2025-07-25 [pcb] minor routing improvements
2025-07-28 [frame] update cad files
2025-07-28 [bom] update link for solder paste
2025-07-28 [bom] replace solder paste and m2 set with cheaper alternative
2025-07-28 [bom] update lcsc components and total
2025-07-28 [bom] update tax
2025-07-28 [pcb] manufacturing constraints and cleanup
2025-07-28 [pcb] update commit silkscreen
2025-10-13 [controller] firmware updates and fixes
2025-10-13 [pcb] schematic v2
2025-10-13 [pcb] schematic v2: footprint/part assignments
2025-10-13 [pcb] pcb v2: component placement
2025-10-13 [pcb] drc fixes
2026-06-15 add bom v2
2026-06-30 bom: add ESP32 wifi antenna
